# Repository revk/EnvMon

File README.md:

Environmental monitoring with OLED display working over MQTT

Note that this is the original version, designed for 1.5 mono OLED display.

* Uses ESP32-RevK library for MQTT/settings
* Uses 128x128 1.5" OLED display
* Uses SCD30 CO2 sensor
* Used DS18B20 Temp sensor

The design makes for a small cuboid unit powered by a USB cable with
an OLED display showing CO2, temperature, and humidity.

It can also be set with CO2 level and temperature levels which can trigger
MQTT messages allowing control of fans or heating systems.

The design is intended to work with a leaded external DS18B20 temperature
sensor, allowing more accurate temperature to be measured where needed and
without heat from components impacting the reading.

The CO2 sensor used is an expensive NDIR module providing accurate CO2
measurement which is not fooled by farts, etc.

A PCB design is included based on milling tracks. There is also a PCB
design in the ESP32-OLED project which uses a professionally printed
PCB layout.

(c) 2019-21 Andrews & Arnold Ltd, Adrian Kennard. See LICENSE file (GPL).

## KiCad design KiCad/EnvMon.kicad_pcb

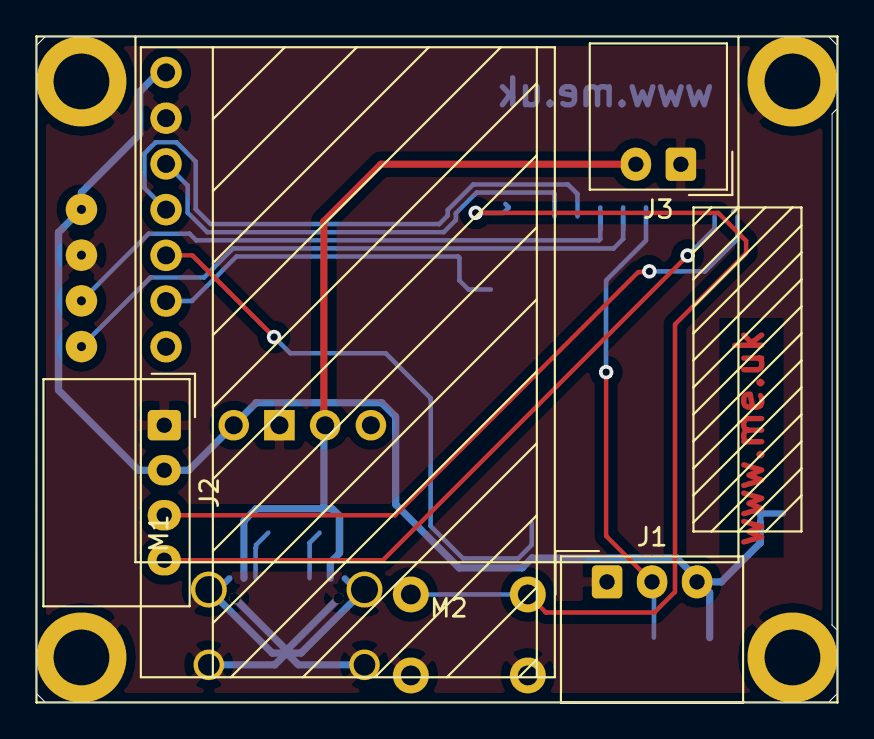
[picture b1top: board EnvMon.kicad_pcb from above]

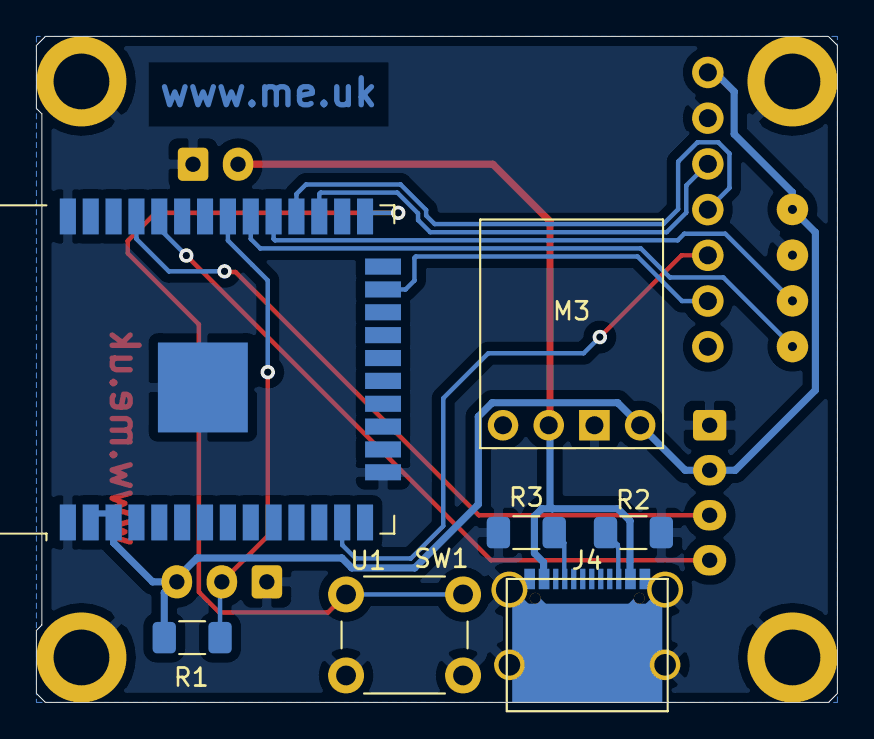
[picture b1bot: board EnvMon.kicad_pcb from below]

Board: 2 copper layers, 44.5 x 37.0 mm, 12 parts (7 on the bottom side), 15 nets.

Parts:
J1: DS18B20; Molex_SPOX_5268-03A_1x03_P2.50mm_Horizontal
J2: Prog; Molex_SPOX_5268-04A_1x04_P2.50mm_Horizontal
J3: 12V; Molex_SPOX_5268-02A_1x02_P2.50mm_Horizontal
J4: USB-C; USC16-TR-Round
M1: SCD30
M2: OLED1.5-I2C
M3: D24V5F3
R1: 4K7; R_1206_3216Metric_Pad1.30x1.75mm_HandSolder
R2, R3: 5K1; R_1206_3216Metric_Pad1.30x1.75mm_HandSolder
SW1: GPIO0; SW_PUSH_6mm_H4.3mm
U1: ESP32-WROOM-32

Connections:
+3V3: J1.3, J2.2, M1.1, M2.1, M3.4, R1.1, U1.2, U1.3
/TEMP: J1.2, R1.2, U1.31
/VBUS: J3.2, J4.A4, J4.A9, J4.B4, J4.B9, M3.2
GND: J1.1, J2.1, J3.1, J4.A1, J4.A12, J4.B1, J4.B12, J4.S1, M1.2, M2.2, M2.S, M3.3, R2.2, R3.2, SW1.2, U1.1, U1.15, U1.38, U1.39
unnamed: J2.3, U1.35
unnamed: J2.4, U1.34
unnamed: J4.A5, R3.1
unnamed: J4.B5, R2.1
unnamed: M1.3, U1.27
unnamed: M1.4, U1.28
unnamed: M1.5, U1.13
unnamed: M1.6, U1.23
unnamed: M2.4, U1.29
unnamed: M2.5, U1.30
unnamed: SW1.1, U1.25

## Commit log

2019-05-23 Initial files
2019-05-23 Tweaks
2019-08-26 Restart project for ESP32
2019-08-26 Added
2019-08-26 Library update
2019-08-26 Start testing
2019-08-26 Crashy
2019-08-26 Less crashy
2019-08-26 Yay, works!
2019-08-26 Tidy
2019-09-07 Working on DS18B20
2019-09-07 DS18B20 - yay!
2019-09-07 Report on change
2019-09-07 Rounding
2019-09-07 Separate tasks, and consistent rounding and hysteresis rules.
2019-09-07 Tweak
2019-09-07 Getting started on OLED
2019-09-07 Test
2019-09-07 Try again
2019-09-07 Try taht
2019-09-07 Remove
2019-09-07 Back
2019-09-07 Add back
2019-09-07 Settings for the OLED, next for fonts and so on.
2019-09-07 OLED font, and starting on layout
2019-09-07 Iniitial version with display
2019-09-07 Wroking
2019-09-07 Line up
2019-09-08 Timezone
2019-09-08 No Z
2019-09-08 Souped up
2019-09-08 Fahrenheit
2019-09-08 Typo# Please enter the commit message for your changes. Lines starting
2019-09-08 Limit
2019-09-08 Bug fix
2019-09-08 Faster
2019-09-08 Nice fonts
2019-09-08 Try slower as some errors on OLED
2019-09-08 My hysteresis
2019-09-08 100k
2019-09-08 Faster OLED update as one block data I2C transfer
2019-09-08 Spacing tweak
2019-09-09 New PCB design
2019-09-09 Name
2019-09-09 Name change
2019-09-09 New PCB
2019-09-09 Revised defaults to match PCB
2019-09-10 Display flip option
2019-09-10 Damping
2019-09-10 Send every hour anyway
2019-09-11 New logo and config
2019-09-11 Initial 3D print design for testing
2019-09-11 Revised
2019-09-11 Minor revisions
2019-09-11 Looks better at shallower angle
2019-09-12 Minor improvements
2019-09-12 Change defaults foe new PCb layout
2019-09-12 Centre on OLED
2019-09-12 * for over CO2 level
2019-09-12 Picture added
2019-09-12 Tweak to make position of ESP32 clearer
2019-09-12 Sanity check
2019-09-13 To close to pad
2019-09-13 Partition table
2019-09-13 Update for contrast control
2019-09-13 Contrast control
2019-09-13 CO2 module commands for calibration/offsets
2019-09-13 CO2 module commands for calibration and testing
2019-09-13 Submodule loading
2019-09-13 Startup bugs
2019-09-13 Slightly more sentred
2019-09-14 Allow a version without OLED
2019-09-14 Bugfix
2019-09-14 Correct USB connector spacing
2019-09-14 Correct no-oled box cut
2019-09-15 Air hole when no OLED
2019-09-15 Text change
2019-09-16 Default constrast
2019-09-16 Typo
2019-09-17 Night/day
2019-09-17 Correct error message
2019-09-17 Was not showing some stuff due to timing
2019-09-17 Starting C code for logging and graphing
2019-09-17 Comment
2019-09-17 Blank apps with libraries and includes in place
2019-09-17 Making a start
2019-09-17 Getting MQTT now
2019-09-18 Logging working
2019-09-18 Logging
2019-09-18 Started on graphing
2019-09-20 New OLED ligrary
2019-09-20 Actually showing fan now
2019-09-20 Need to mess with scale still
2019-09-20 Started on graphs, needs axis and a few bits
2019-09-20 Needs axis
2019-09-21 Fixed contrast logic
2019-09-21 debug
2019-09-21 Fucked up axis
2019-09-21 Still messed up
2019-09-21 Better
2019-09-21 Nice
2019-09-21 Headings
2019-09-21 Ref line
2019-09-23 End of day
2019-09-23 Blobs on current value
2019-09-25 Moved logo
2019-09-25 D'Oh
2019-10-06 Changed to USB-C (still needs 3D case updating)
2019-10-08 New case
2019-10-09 Revised USB-C connector with 5.1k pull downs (good luck)
2019-10-09 Corrected USB-C
2019-10-11 Minor tweaks
2019-10-12 User guide and other updates
2019-10-12 Added switch for GPIO0
2019-10-12 USB-C
2019-10-12 Slice at different height
2019-10-12 Tweak PCB
2019-10-13 Updated parts
2019-10-13 Update image
2019-10-27 Format string now used
2019-11-23 Template
2021-02-26 (untested) added heating control MQTT
2021-02-26 Heat reversed
2021-02-27 Power control resends periodically
2021-02-28 Quiet if heat temp not set for period day/night
2021-02-28 Silly error
2021-03-04 Started work on KiCad PCB design
2021-03-04 First version
2021-03-08 New library
2021-03-08 New library parts
2021-03-08 Corrected tx/rx
2021-03-08 Tidied schematic diagrams
2021-03-08 Fix hole sizes, duh
2021-03-09 Started on new Documents
2021-03-09 More on README
2021-03-09 Rework for new PCB and colour OLED
2021-03-09 spox headers
2021-03-13 Moved to new ESP32-EnvMon
